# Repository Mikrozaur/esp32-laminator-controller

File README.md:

# ESP32 Roll Laminator Controller

[Русская версия](README_ru.md)

Modern replacement controller for inexpensive roll laminators based on **ESP32-C3** and **ESPHome**.

The project replaces the original controller board with a fully programmable, modular, and repairable solution built from standard components.

---

## Project Goals

- High reliability
- Electrical safety
- Easy maintenance and repair
- Use of widely available components
- Complete separation of high-voltage and low-voltage circuits
- Home Assistant integration
- Open-source hardware and firmware

---

## Current Status

**Version:** 1.0

✔ Hardware completed

✔ ESPHome firmware completed

✔ Control algorithms completed

✔ Preliminary temperature calibration completed

⏳ Fine temperature calibration and long-term testing remain.

---

## Main Features

- Heater temperature control
- Motor forward / reverse control
- Temperature adjustment using a potentiometer
- Analog temperature meter support
- Two status LEDs (PREHEAT / WORK)
- NTC 100k B4300 temperature sensor
- Home Assistant integration through ESPHome
- Simple modular architecture
- Standard relay module support
- Easy assembly on perfboard

---

## Safety

The controller was designed with electrical safety as one of its primary goals.

Unlike the original controller board, **all high-voltage (220 VAC) circuitry has been removed from the control electronics**.

The ESP32 board, switches, potentiometer, LEDs, and temperature sensor operate exclusively from **3.3 V / 5 V**.

The only part connected to mains voltage is the external **4-channel relay module**, which switches:

- Heater
- Motor power
- Motor direction

This architecture significantly improves safety, simplifies debugging, and makes future repairs much easier.

---

## Hardware
  
Controller:

- ESP32-C3 LuatOS Core

Temperature sensor:

- Glass NTC 100k B4300

Voltage regulator:

- AMS1117-3.3

Relay module:#

- Standard 4-channel relay board
- Active LOW inputs

---

## GPIO Mapping

| GPIO | Function |
|------|----------|
| GPIO0 | NTC temperature sensor |
| GPIO1 | Potentiometer |
| GPIO2 | MASTER switch |
| GPIO3 | SEAL switch |
| GPIO4 | Heater relay |
| GPIO5 | Reverse relay |
| GPIO6 | Direction switch |
| GPIO7 | Analog meter (PWM) |
| GPIO20 | PREHEAT LED |
| GPIO21 | WORK LED |

Unused GPIO:

- GPIO8
- GPIO9
- GPIO12
- GPIO13
- GPIO18
- GPIO19

---

## Relay Module

The project uses a standard **4-channel Active LOW relay module**.

Logic:

- GPIO LOW → Relay ON
- GPIO HIGH → Relay OFF

ESPHome configuration:

- `inverted: true`
- `restore_mode: ALWAYS_OFF`

This guarantees that all relays remain OFF immediately after power-up or reset.

---

## Repository Structure

```
Firmware/
    ESPHome YAML

Hardware/
    Schematics
    PCB
    KiCad project

docs/
    Technical specification
    Calibration notes

Images/
    Photos
    Schematics
```

---

## Requirements

- ESPHome
- Home Assistant (optional)
- ESP32-C3
- 5V power supply
- Standard 4-channel relay module

---

## Future Improvements

- Final temperature calibration
- Long-term reliability testing
- PCB revision
- Optional WS2812 status indicator
- Additional Home Assistant entities

---

## License

This project is released under the MIT License.

Feel free to use, modify and improve it.

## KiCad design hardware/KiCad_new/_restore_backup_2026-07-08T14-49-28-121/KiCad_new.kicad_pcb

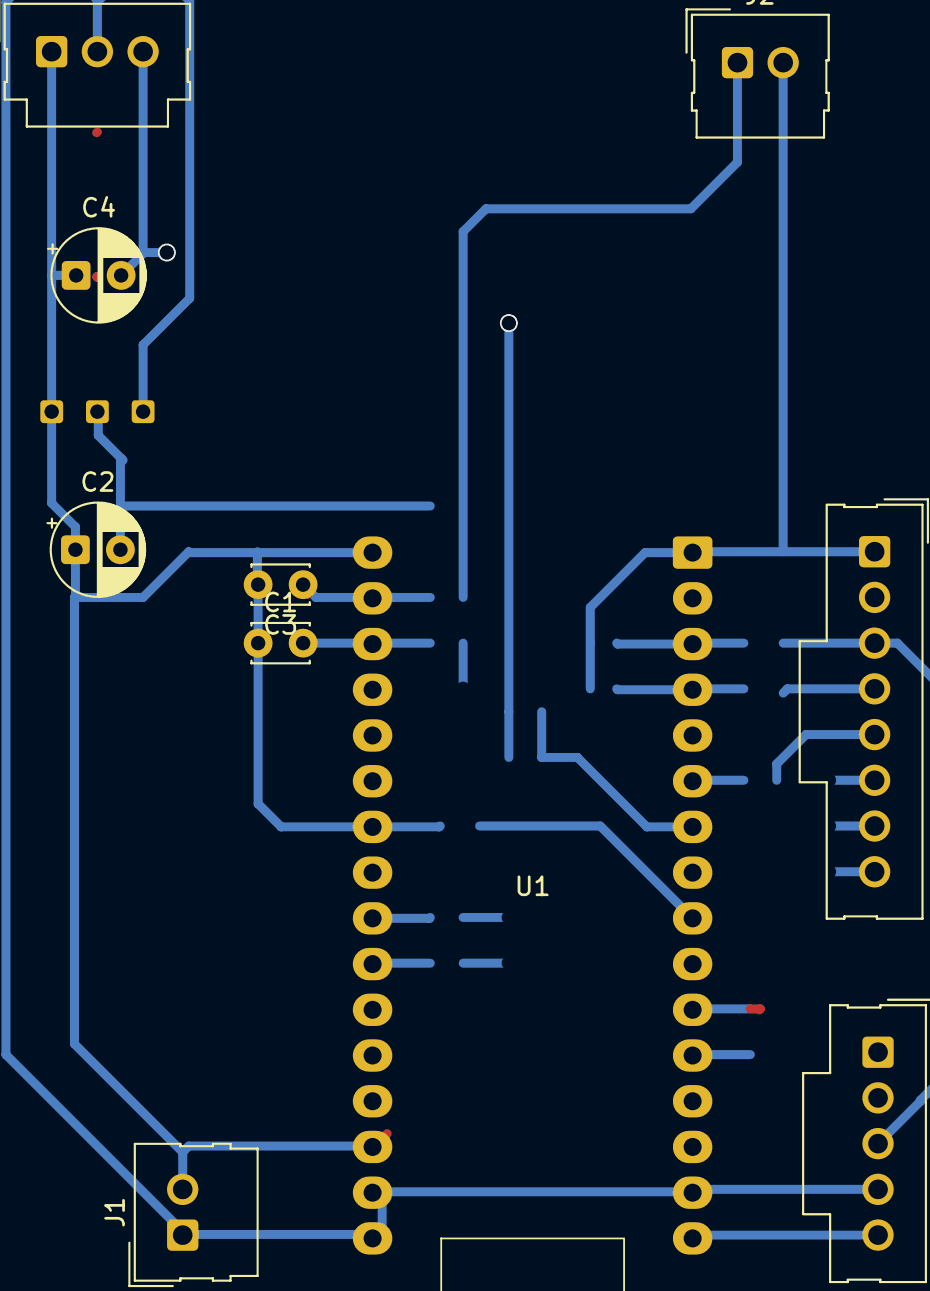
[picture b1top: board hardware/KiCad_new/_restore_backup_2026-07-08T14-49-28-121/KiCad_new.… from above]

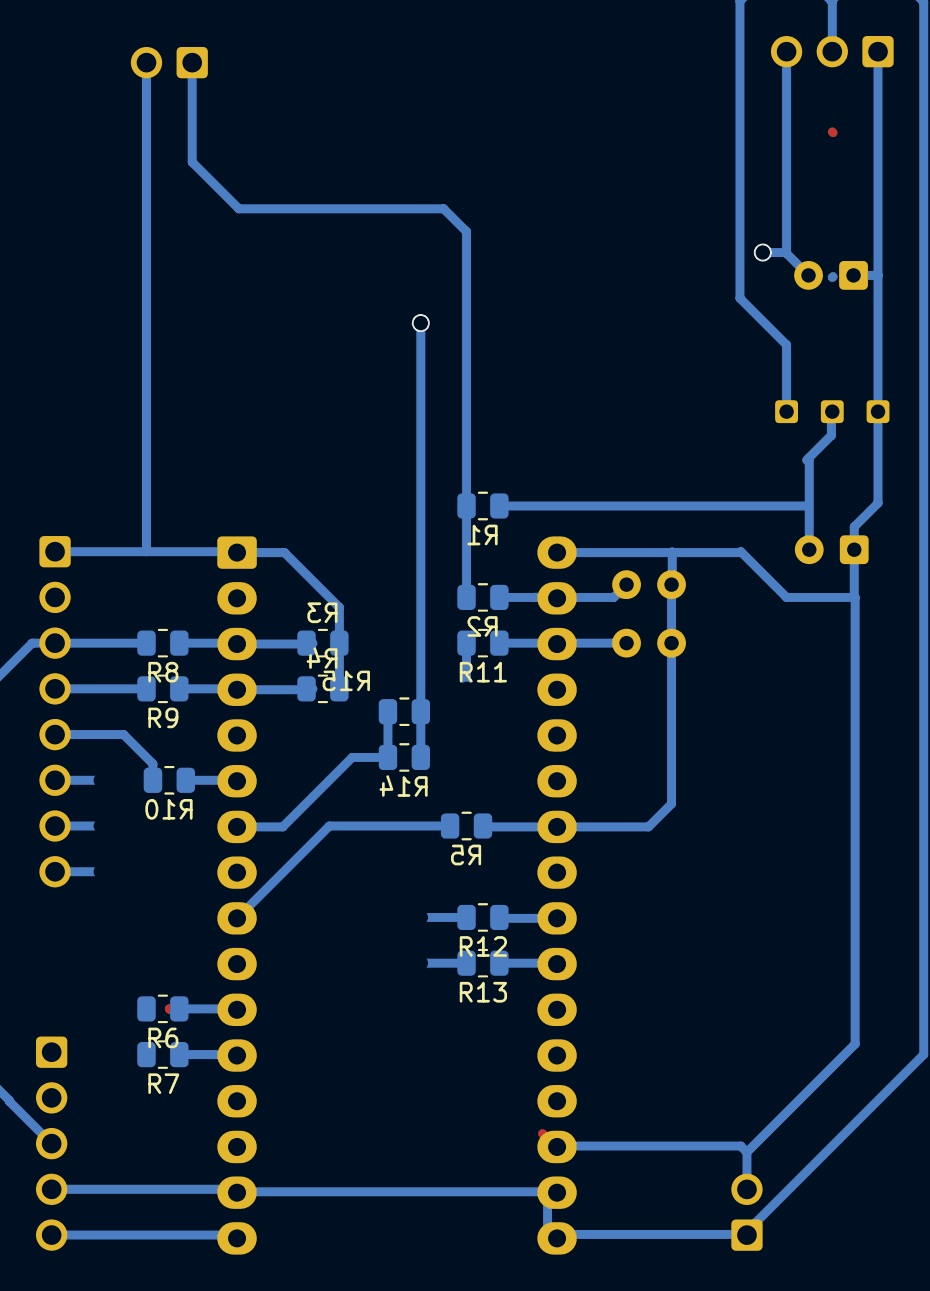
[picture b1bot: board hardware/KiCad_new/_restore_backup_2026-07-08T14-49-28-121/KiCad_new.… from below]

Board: 2 copper layers, 26 parts (15 on the bottom side), 24 nets.

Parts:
C1, C3: 100n; C_Disc_D3.0mm_W2.0mm_P2.50mm
C2, C4: 100uF; CP_Radial_D5.0mm_P2.50mm
J1: J1 Power; Molex_SL_171971-0002_1x02_P2.54mm_Vertical
J2: J2 NTC; Molex_SL_171971-0002_1x02_P2.54mm_Vertical
J3: Meter; Molex_SL_171971-0003_1x03_P2.54mm_Vertical
J4: Relay Module; Molex_SL_171971-0005_1x05_P2.54mm_Vertical
J5: Control Panel; Molex_SL_171971-0008_1x08_P2.54mm_Vertical
R1: 47k; R_0805_2012Metric
R2, R11: 100; R_0805_2012Metric
R3, R4, R5, R15: 10k; R_0805_2012Metric
R6, R7, R8, R9, R10, R12, R13: 470; R_0805_2012Metric
R14: 4,7к; R_0805_2012Metric
U1: ESP32-C3 Dev Board; ESP32-C3_LuatOS
U2: AMS1117; Ams1117 module

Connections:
GND: C1.1, C2.1, C3.2, C4.1, J1.2, J2.2, J3.1, J4.5, J5.1, R3.2, R4.2, R5.2, U1.1 (GND), U1.9 (GND), U1.16 (GND), U1.17 (GND), U1.23 (GND), U1.30 (GND), U2.3 (Gnd)
unnamed: J1.1, J3.2, J4.4, U1.15 (+5v), U1.31 (PWR), U1.32 (+5v), U2.1 (VIn_5v)
unnamed: J2.1, R1.2, R2.2
unnamed: C4.2, J3.3, R14.1, R15.1
unnamed: J4.1, R7.2
unnamed: J4.2, R6.2
unnamed: J4.3, J5.3, R8.2
unnamed: J5.2, U1.10 (+3.3v)
unnamed: J5.4, R9.2
unnamed: J5.5, R10.2
unnamed: J5.6, R11.2
unnamed: J5.7, R12.2
unnamed: J5.8, R13.2
unnamed: C3.1, R2.1, U1.18 (GPIO0)
unnamed: C1.2, R11.1, U1.19 (GPIO1)
unnamed: R3.1, R8.1, U1.3 (GPIO2)
unnamed: R4.1, R9.1, U1.4 (GPIO3)
unnamed: R7.1, U1.12 (GPIO4)
unnamed: R6.1, U1.11 (GPIO5)
unnamed: R5.1, R10.1, U1.6 (GPIO6)
unnamed: R14.2, R15.2, U1.7 (GPIO7)
unnamed: R13.1, U1.26 (GPIO13)
unnamed: R12.1, U1.25 (GPIO21)
unnamed: C2.2, R1.1, U2.2 (VOut_3.3v)

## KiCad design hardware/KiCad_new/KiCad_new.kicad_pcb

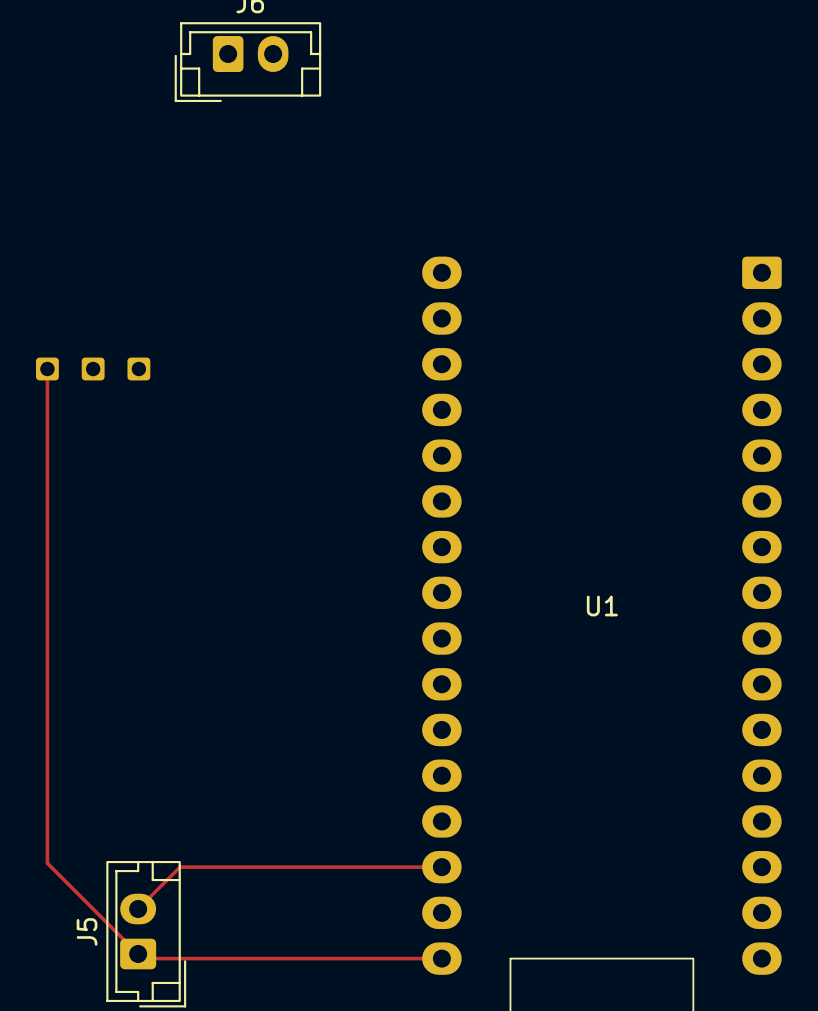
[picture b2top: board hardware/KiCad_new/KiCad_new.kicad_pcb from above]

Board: 2 copper layers, 4 parts (0 on the bottom side), 3 nets.

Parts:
J5: Power; JST_EH_B2B-EH-A_1x02_P2.50mm_Vertical
J6: NTC; JST_EH_B2B-EH-A_1x02_P2.50mm_Vertical
P1: Ams1117 module
U1: ESP32-C3 LuatOS; ESP32-C3_LuatOS

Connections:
unnamed: J5.1, P1.1 (VIn_5v), U1.32 (+5v)
unnamed: J5.2, J6.1, U1.17 (GND), U1.24 (GND), U1.30 (GND)
unnamed: J6.2, U1.18 (GPIO0)

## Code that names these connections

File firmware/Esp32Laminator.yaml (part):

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    name: "MASTER"

    pin:
      number: GPIO2
      mode:
        input: true
      inverted: true
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    name: "SEAL"

    pin:
      number: GPIO6
      mode:
        input: true
      inverted: true
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    name: "DIR"
    internal: true
    pin:
      number: GPIO3
      mode:
        input: true
 #     inverted: true
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    id: heater_relay
    name: "Heater Relay"
    pin: 
      number: GPIO5
      inverted: true
    restore_mode: ALWAYS_OFF
# --------------------------------------------------------
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    name: "Reverse Relay"
    internal: true
    pin:
      number: GPIO4
      inverted: true
    restore_mode: ALWAYS_OFF

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    id: led_preheat_out

    pin:
      number: GPIO21
      inverted: true

# --------------------------------------------------------
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  - platform: ledc
    id: meter_pwm

    pin: GPIO7

    frequency: 1000 Hz

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
    internal: true

    pin: GPIO0

    attenuation: auto

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
    name: "Potentiometer"

    pin: GPIO1

    update_interval: 100ms

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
